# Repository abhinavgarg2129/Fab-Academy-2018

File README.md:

# Fablab
Original Files of my work for WEEK-4

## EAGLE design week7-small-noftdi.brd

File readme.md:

# Fab Academy 2018
Original Files - week 6

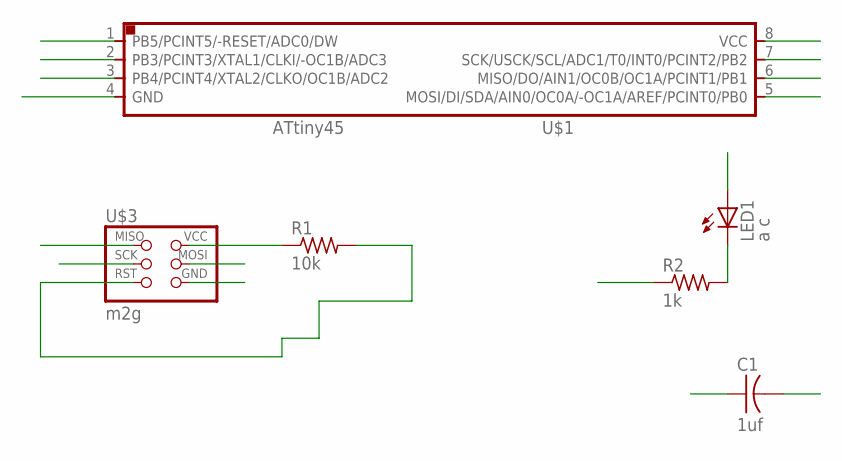
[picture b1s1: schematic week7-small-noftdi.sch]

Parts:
C1: 1uf; C1206FAB
LED1: a c; LED1206FAB
R1: 10k; R1206FAB
R2: 1k; R1206FAB
U$1: tt45; SOIC8
U$3: m2g; 2X03SMD

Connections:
GND: C1.2, R2.1, U$1.4 (GND), U$3.6 (GND)
MISO: U$1.6 (MISO/DO/AIN1/OC0B/OC1A/PCINT1/PB1), U$3.1 (MISO)
MOSI: U$1.5 (MOSI/DI/SDA/AIN0/OC0A/-OC1A/AREF/PCINT0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), U$3.4 (MOSI)
unnamed: LED1.2 (C), R2.2
RST: R1.2, U$1.1 (PB5/PCINT5/-RESET/ADC0/DW), U$3.5 (RST)
SCK: U$1.7 (SCK/USCK/SCL/ADC1/T0/INT0/PCINT2/PB2), U$3.3 (SCK)
VCC: C1.1, R1.1, U$1.8 (VCC), U$3.2 (VCC)
XTAL1: LED1.1 (A), U$1.2 (PB3/PCINT3/XTAL1/CLKI/-OC1B/ADC3)
XTAL2: U$1.3 (PB4/PCINT4/XTAL2/CLKO/OC1B/ADC2)

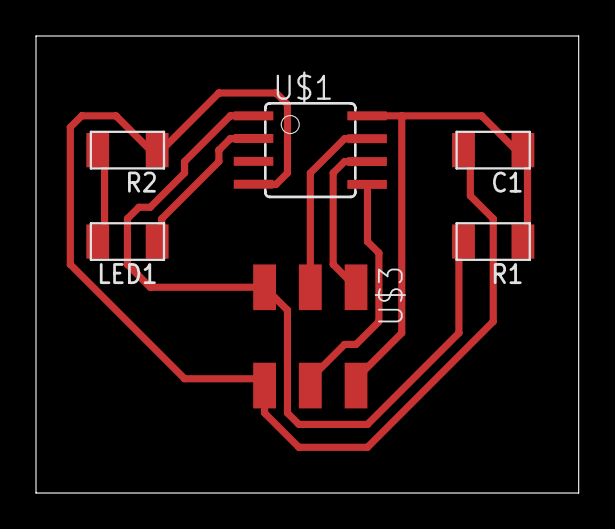
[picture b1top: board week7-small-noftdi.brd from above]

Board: 2 copper layers, 30.1 x 25.4 mm, 6 parts (0 on the bottom side), 8 nets.

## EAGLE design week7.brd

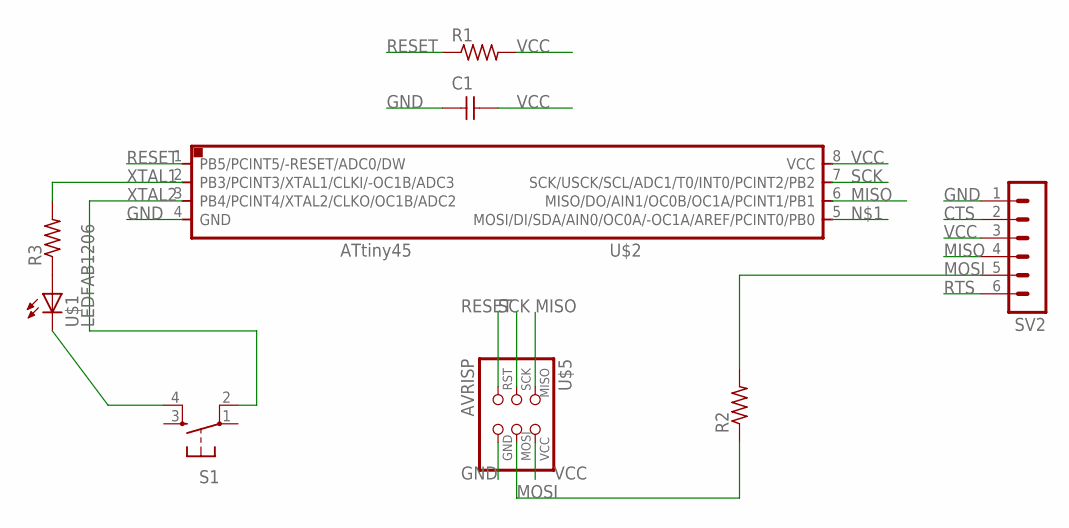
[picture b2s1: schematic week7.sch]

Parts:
C1: CAP-UNPOLARIZED; C1206
R1, R2, R3: RES-US1206FAB; R1206FAB
S1: 6MM_SWITCH6MM_SWITCH; 6MM_SWITCH
SV2: MA06-1
U$1: LEDFAB1206; LED1206FAB
U$2: ATTINY45SI; SOIC8
U$5: AVRISP; 2X03

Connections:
CTS: SV2.2
GND: C1.1, S1.4 (S1), SV2.1, U$1.2 (C), U$2.4 (GND), U$5.6 (GND)
MISO: SV2.4, U$2.6 (MISO/DO/AIN1/OC0B/OC1A/PCINT1/PB1), U$5.1 (MISO)
MOSI: R2.1, R2.2, SV2.5, U$5.4 (MOSI)
unnamed: R3.1, U$1.1 (A)
RESET: R1.1, U$2.1 (PB5/PCINT5/-RESET/ADC0/DW), U$5.5 (RST)
RTS: SV2.6
SCK: U$2.7 (SCK/USCK/SCL/ADC1/T0/INT0/PCINT2/PB2), U$5.3 (SCK)
VCC: C1.2, R1.2, SV2.3, U$2.8 (VCC), U$5.2 (VCC)
XTAL1: R3.2, U$2.2 (PB3/PCINT3/XTAL1/CLKI/-OC1B/ADC3)
XTAL2: S1.2 (P1), U$2.3 (PB4/PCINT4/XTAL2/CLKO/OC1B/ADC2)

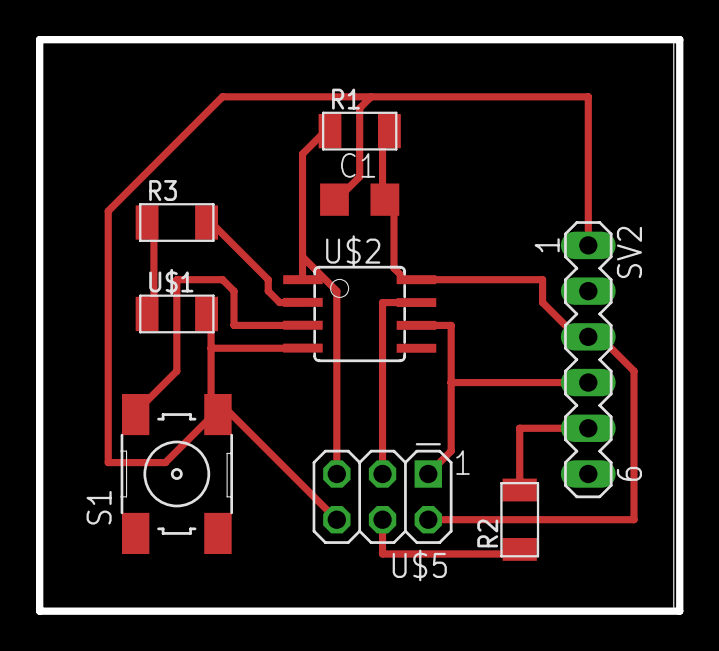
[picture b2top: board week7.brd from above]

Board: 2 copper layers, 35.6 x 31.8 mm, 9 parts (0 on the bottom side), 9 nets.

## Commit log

2018-02-14 solidworks file of strap
2018-02-14 inkscape file of strap
2018-02-14 Rename abhinav-garg.md to readme.md
2018-05-29 Rename processign.pde.md to processing.pde
